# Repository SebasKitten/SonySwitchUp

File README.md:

# SonySwitchUp

SonySwitchUp aims to put modern hardware inside a **Sony VAIO UX**, replacing its original motherboard with a **Nintendo Switch OLED motherboard**.

The project also explores using a Switch motherboard as the foundation for a cyberdeck or other custom device, much as you might use a Raspberry Pi or LattePanda. The VAIO UX build is a practical example of that idea, with the aim of showing how adaptable Switch hardware can be.

The goal is to develop both a **VAIO UX conversion kit** and **example designs others can build on**. We hope these files inspire people to reuse, optimize, or modify the adapters for their own projects. A key motivation is putting secondhand Switch hardware to work in affordable custom builds.

## MIPI display adapter

The MIPI adapter **repins the Switch OLED motherboard's display FPC connector** to match the **Startek KD050HDOIN116-C000-a replacement AMOLED screen** used in this build. It routes the MIPI DSI display signals to the panel's pinout and provides the associated power switching and control connections.

This revision is designed for that specific screen, whose [specification is included](hardware/mipi-adapter/revD/sources/panel_spec.pdf).

- [Rev D design files](hardware/mipi-adapter/revD/) — open `mipi_adapter_revD.kicad_pro` in KiCad 10.
- [Assembly and power notes](hardware/mipi-adapter/revD/IMPORTANT.txt)
- [Design changes and recorded checks](hardware/mipi-adapter/revD/CHANGELOG.md)

## Status

**Work in progress.** 

Please do not use these files yet. as I am mostly developing locally and this is currently just a placeholder.

I've already gotten new revisions done and will soon be in the stages of ordering prototypes and testing.

this project will have both a MIPI Adapter. and have an USB HID controller to connect the UX Keyboard to any USB device.

Only the MIPI adapter Rev D files are included so far. The adapter is unfinished and has not been validated on powered hardware; the complete VAIO UX kit and other project components will follow as development progresses.

A project license has not been selected yet. Included third-party documents and libraries retain their respective ownership and license terms.

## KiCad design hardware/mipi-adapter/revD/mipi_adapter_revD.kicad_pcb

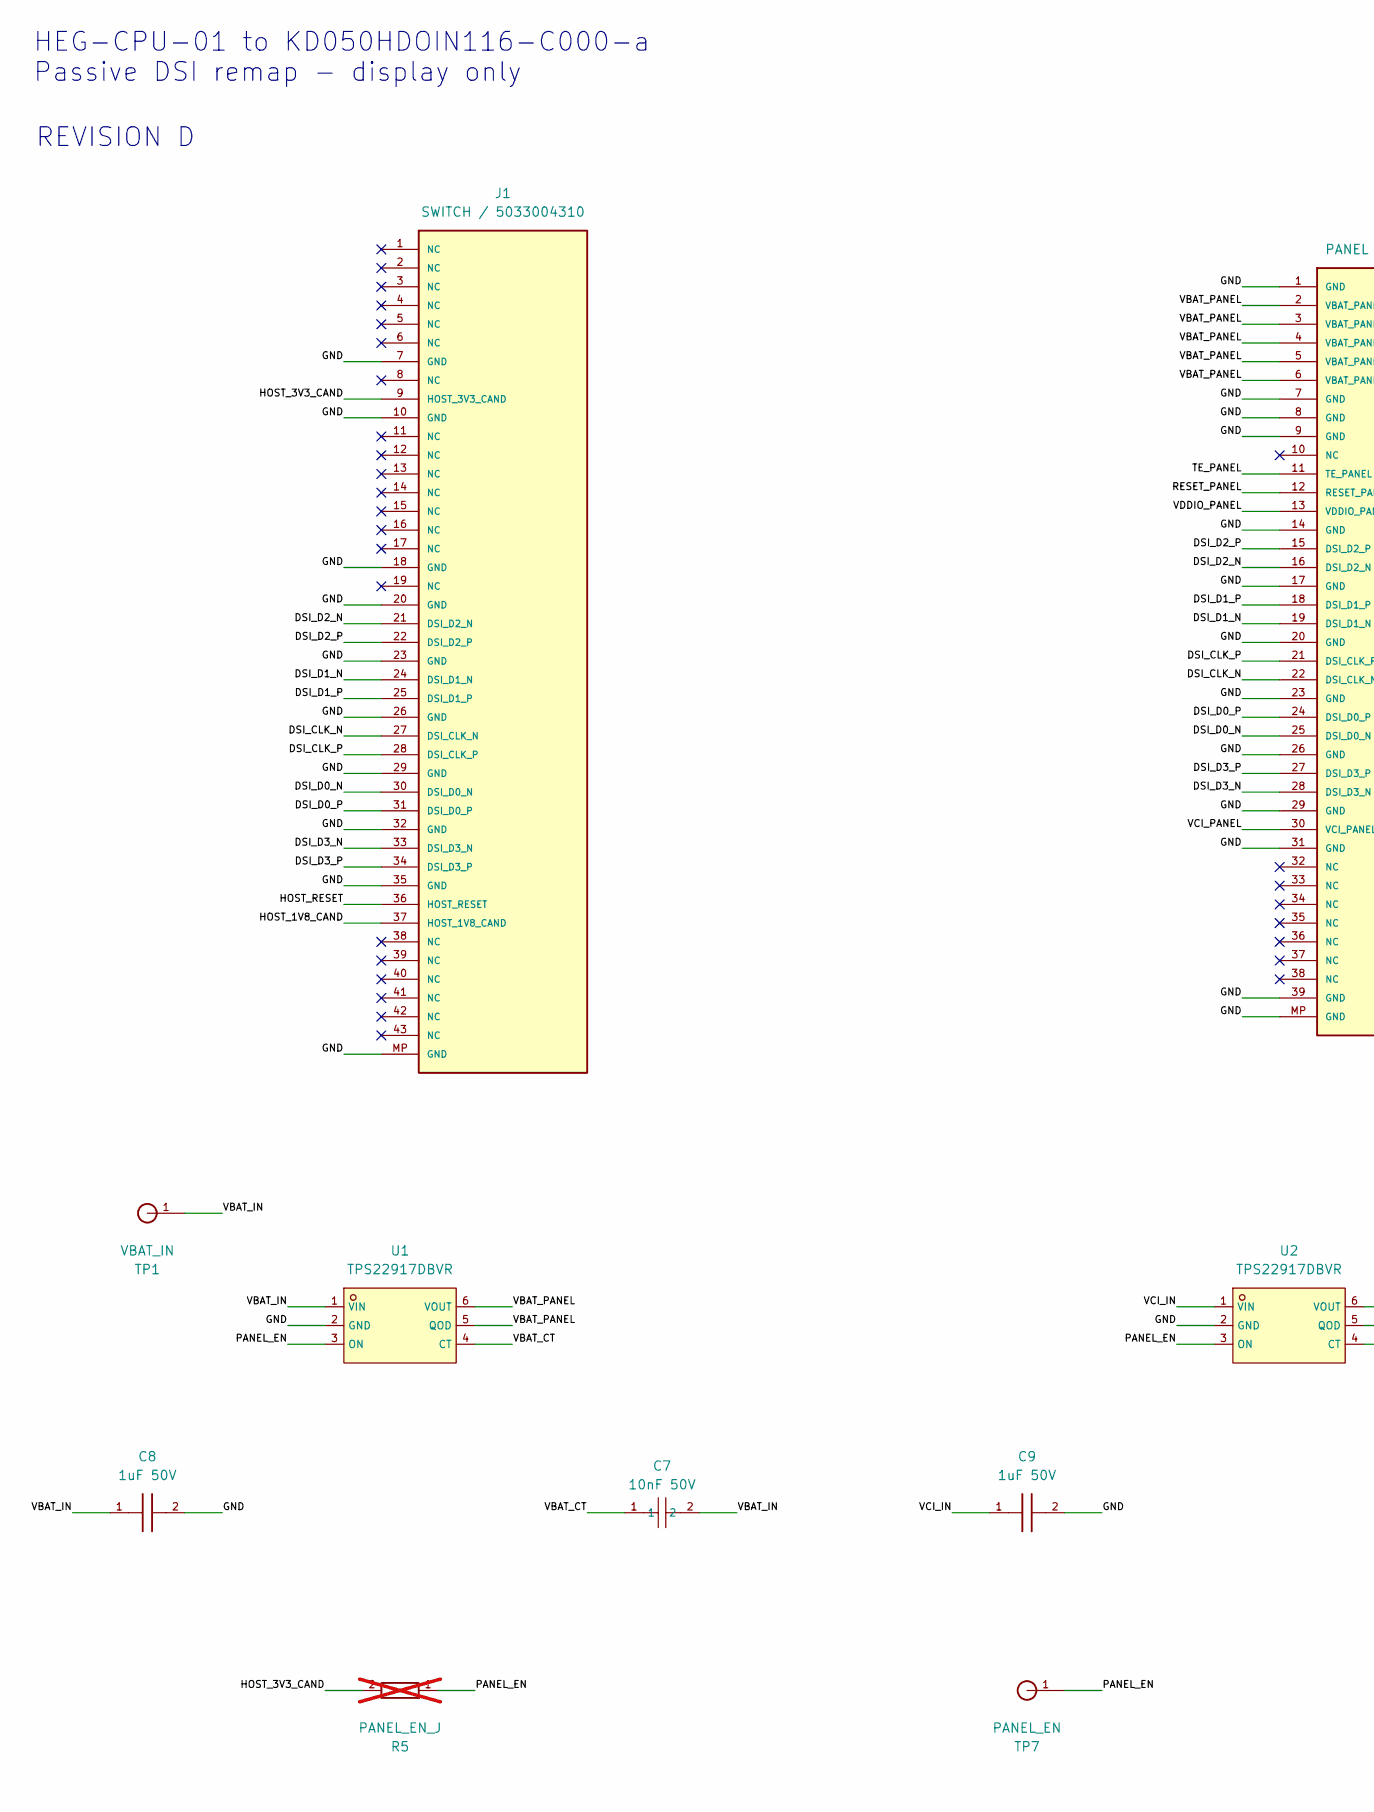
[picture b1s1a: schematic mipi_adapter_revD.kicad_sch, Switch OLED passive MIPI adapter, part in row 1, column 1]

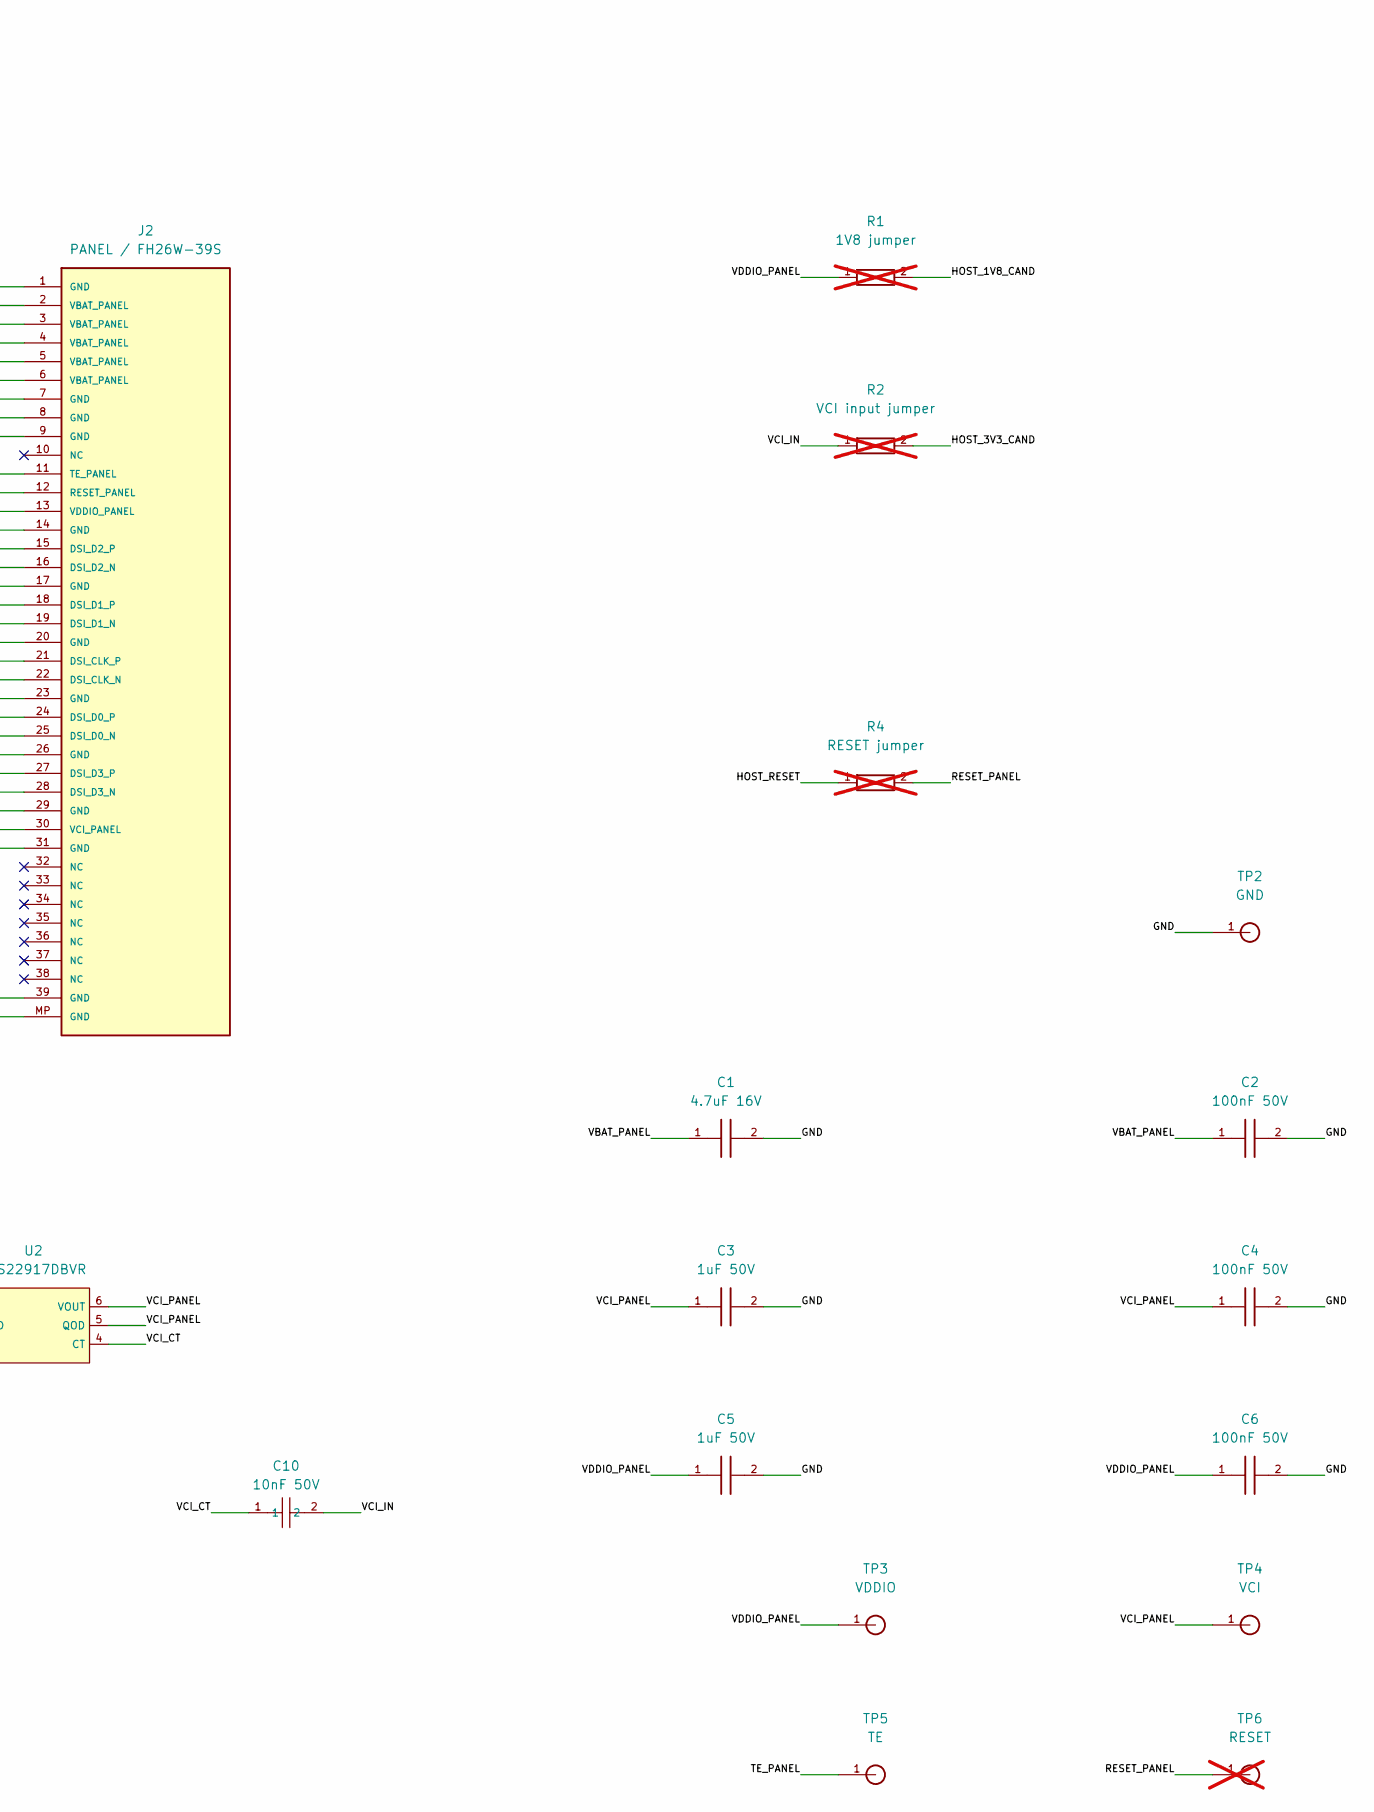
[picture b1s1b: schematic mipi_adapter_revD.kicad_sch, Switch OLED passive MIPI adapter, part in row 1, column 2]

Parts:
C1: 4.7uF 16V; C_0603_1608Metric; LCSC C19666
C2, C4, C6: 100nF 50V; C_0603_1608Metric; LCSC C14663
C3, C5, C8, C9: 1uF 50V; C_0603_1608Metric; LCSC C15849
C7, C10: 10nF 50V; C_0603_1608Metric; LCSC C57112
J1: SWITCH / 5033004310; Molex_503300_4310_front_left_1; LCSC C565041
J2: PANEL / FH26W-39S; Hirose_FH26-39S-0.3SHW_2Rows-39Pins-1MP_P0.60mm_Horizontal; LCSC C92280
R1: 1V8 jumper; R_0603_1608Metric; LCSC C21189; not fitted
R2: VCI input jumper; R_0603_1608Metric; LCSC C21189; not fitted
R4: RESET jumper; R_0603_1608Metric; LCSC C21189; not fitted
R5: PANEL_EN_J; R_0603_1608Metric; LCSC C21189; not fitted
TP1: VBAT_IN; TestPoint_Pad_D1.5mm
TP2: GND; TestPoint_Pad_D1.5mm
TP3: VDDIO; TestPoint_Pad_D1.5mm
TP4: VCI; TestPoint_Pad_D1.5mm
TP5: TE; TestPoint_Pad_D1.5mm
TP6: RESET; TestPoint_Pad_D1.5mm; not fitted
TP7: PANEL_EN; TestPoint_Pad_D1.5mm
U1, U2: TPS22917DBVR; C2681320_SOT-23-6_L2_9-W1_6-P0_95-LS2_8-BR; LCSC C2681320

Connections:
/DSI_CLK_N: J1.27 (DSI_CLK_N), J2.22 (DSI_CLK_N)
/DSI_CLK_P: J1.28 (DSI_CLK_P), J2.21 (DSI_CLK_P)
/DSI_D0_N: J1.30 (DSI_D0_N), J2.25 (DSI_D0_N)
/DSI_D0_P: J1.31 (DSI_D0_P), J2.24 (DSI_D0_P)
/DSI_D1_N: J1.24 (DSI_D1_N), J2.19 (DSI_D1_N)
/DSI_D1_P: J1.25 (DSI_D1_P), J2.18 (DSI_D1_P)
/DSI_D2_N: J1.21 (DSI_D2_N), J2.16 (DSI_D2_N)
/DSI_D2_P: J1.22 (DSI_D2_P), J2.15 (DSI_D2_P)
/DSI_D3_N: J1.33 (DSI_D3_N), J2.28 (DSI_D3_N)
/DSI_D3_P: J1.34 (DSI_D3_P), J2.27 (DSI_D3_P)
/GND: C1.2, C2.2, C3.2, C4.2, C5.2, C6.2, C8.2, C9.2, J1.7 (GND), J1.10 (GND), J1.18 (GND), J1.20 (GND), J1.23 (GND), J1.26 (GND), J1.29 (GND), J1.32 (GND), J1.35 (GND), J1.MP (GND), J2.1 (GND), J2.7 (GND), J2.8 (GND), J2.9 (GND), J2.14 (GND), J2.17 (GND), J2.20 (GND), J2.23 (GND), J2.26 (GND), J2.29 (GND), J2.31 (GND), J2.39 (GND), J2.MP (GND), TP2.1 (1_1), U1.2 (GND), U2.2 (GND)
/HOST_1V8_CAND: J1.37 (HOST_1V8_CAND), R1.2
/HOST_3V3_CAND: J1.9 (HOST_3V3_CAND), R2.2, R5.2
/HOST_RESET: J1.36 (HOST_RESET), R4.1
/PANEL_EN: R5.1, TP7.1 (1_1), U1.3 (ON), U2.3 (ON)
/RESET_PANEL: J2.12 (RESET_PANEL), R4.2, TP6.1
/TE_PANEL: J2.11 (TE_PANEL), TP5.1 (1_1)
/VBAT_CT: C7.1, U1.4 (CT)
/VBAT_IN: C7.2, C8.1, TP1.1 (1_1), U1.1 (VIN)
/VBAT_PANEL: C1.1, C2.1, J2.2 (VBAT_PANEL), J2.3 (VBAT_PANEL), J2.4 (VBAT_PANEL), J2.5 (VBAT_PANEL), J2.6 (VBAT_PANEL), U1.5 (QOD), U1.6 (VOUT)
/VCI_CT: C10.1, U2.4 (CT)
/VCI_IN: C9.1, C10.2, R2.1, U2.1 (VIN)
/VCI_PANEL: C3.1, C4.1, J2.30 (VCI_PANEL), TP4.1 (1_1), U2.5 (QOD), U2.6 (VOUT)
/VDDIO_PANEL: C5.1, C6.1, J2.13 (VDDIO_PANEL), R1.1, TP3.1 (1_1)

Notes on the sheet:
HEG-CPU-01 to KD050HDOIN116-C000-a Passive DSI remap - display only
REVISION D

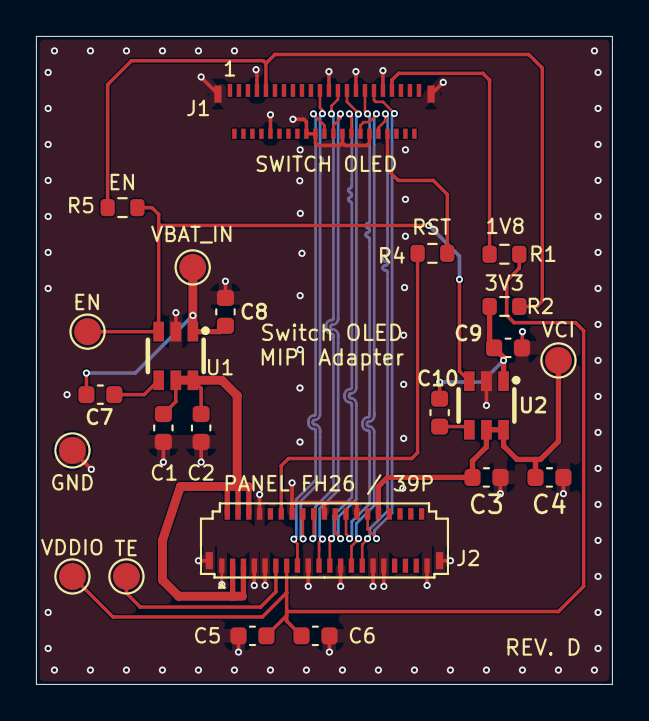
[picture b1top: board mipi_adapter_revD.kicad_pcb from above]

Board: 4 copper layers, 32.0 x 36.0 mm, 24 parts (0 on the bottom side), 24 nets.
